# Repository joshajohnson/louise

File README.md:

# Louise

A project between Josh and RiotPunch to build a 75% alice keyboard with a southpaw numpad.

All the PCB files, case dxfs, and QMK firmware required to build your own are located in this repo.

Thanks to [Warmthoughts](https://www.twitch.tv/warmthoughts) for the photo.

## BOM

| Type     | Spec         | Quantity | Notes                                            |
|----------|--------------|----------|--------------------------------------------------|
| Standoff | M2 x 5mm     | 2        | Wrist Wrest                                      |
| Standoff | M2 x 8mm     | 5        | Foot                                             |
| Standoff | M2 x 10mm    | 3        | Wrist Wrest                                      |
| Standoff | M2 x 12mm    | 12       | Case                                             |
| Screw    | M2 x 5mm     | 4        | Wrist Wrest                                      |
| Screw    | M2 x 6mm     | 40       | Everywhere                                       |
| Encoder  | EC11, 15mm   | 1        | PEC11R-4215F-S0024                               |
| Knob     | Max Dia 18mm | 1        | https://www.aliexpress.com/item/33000897896.html |

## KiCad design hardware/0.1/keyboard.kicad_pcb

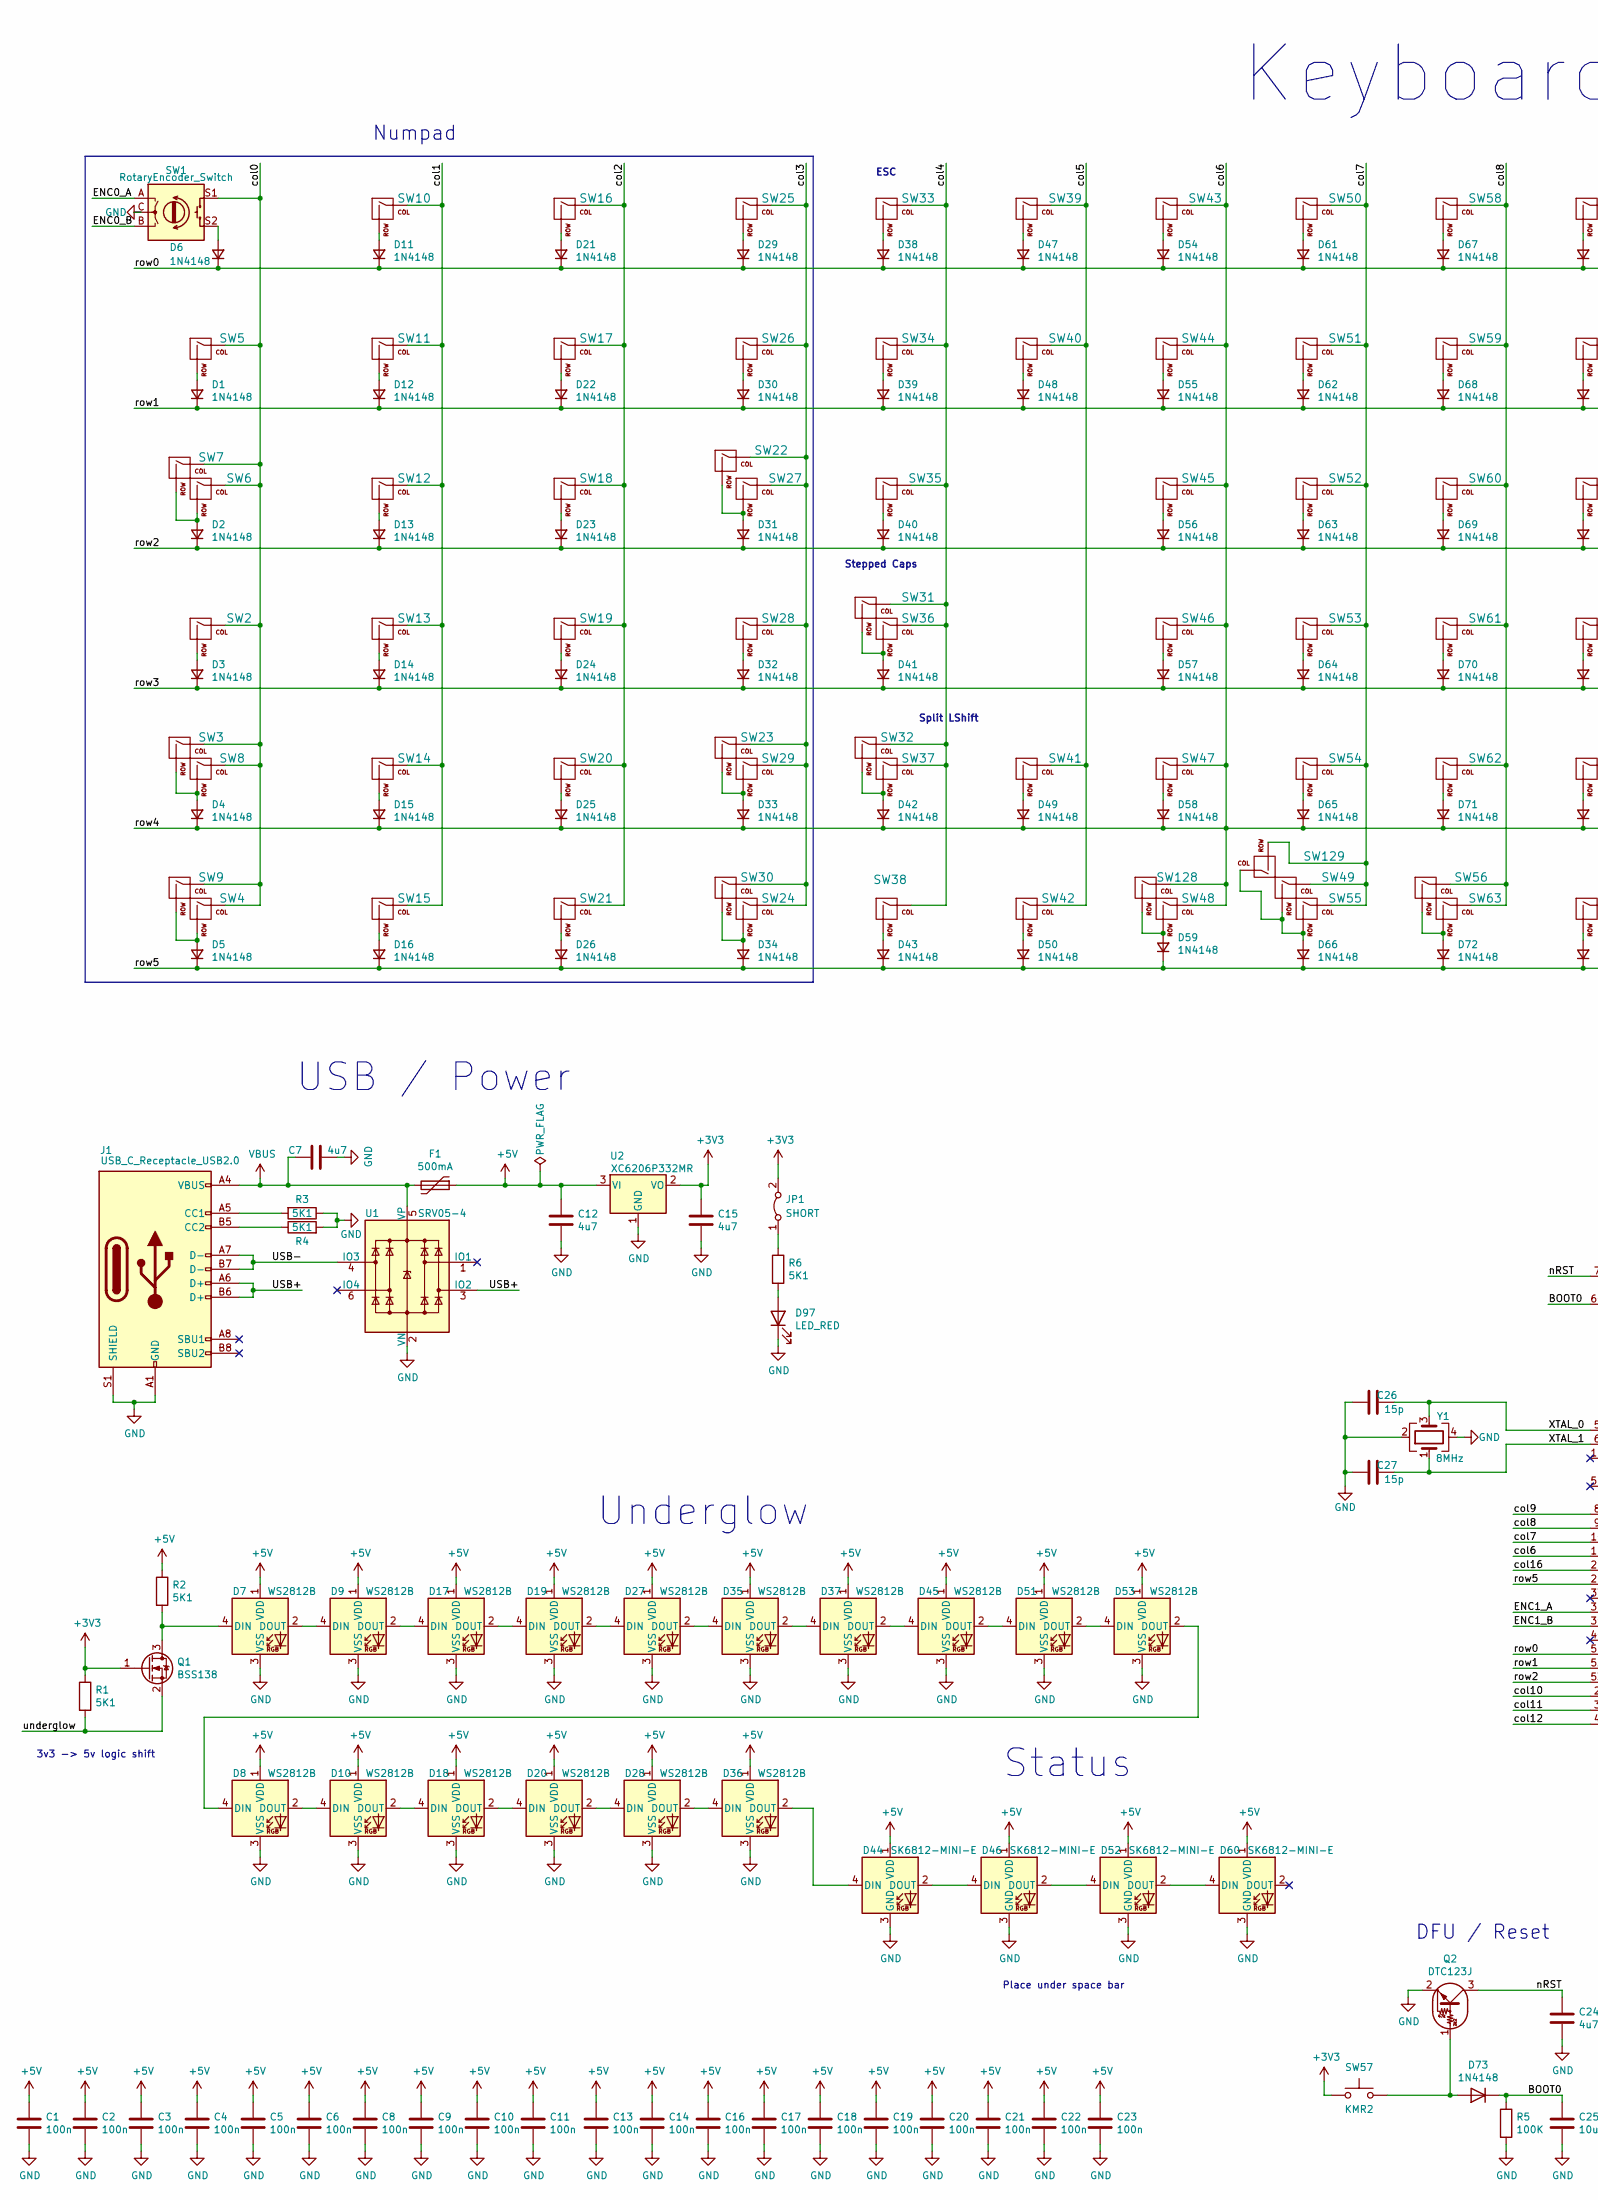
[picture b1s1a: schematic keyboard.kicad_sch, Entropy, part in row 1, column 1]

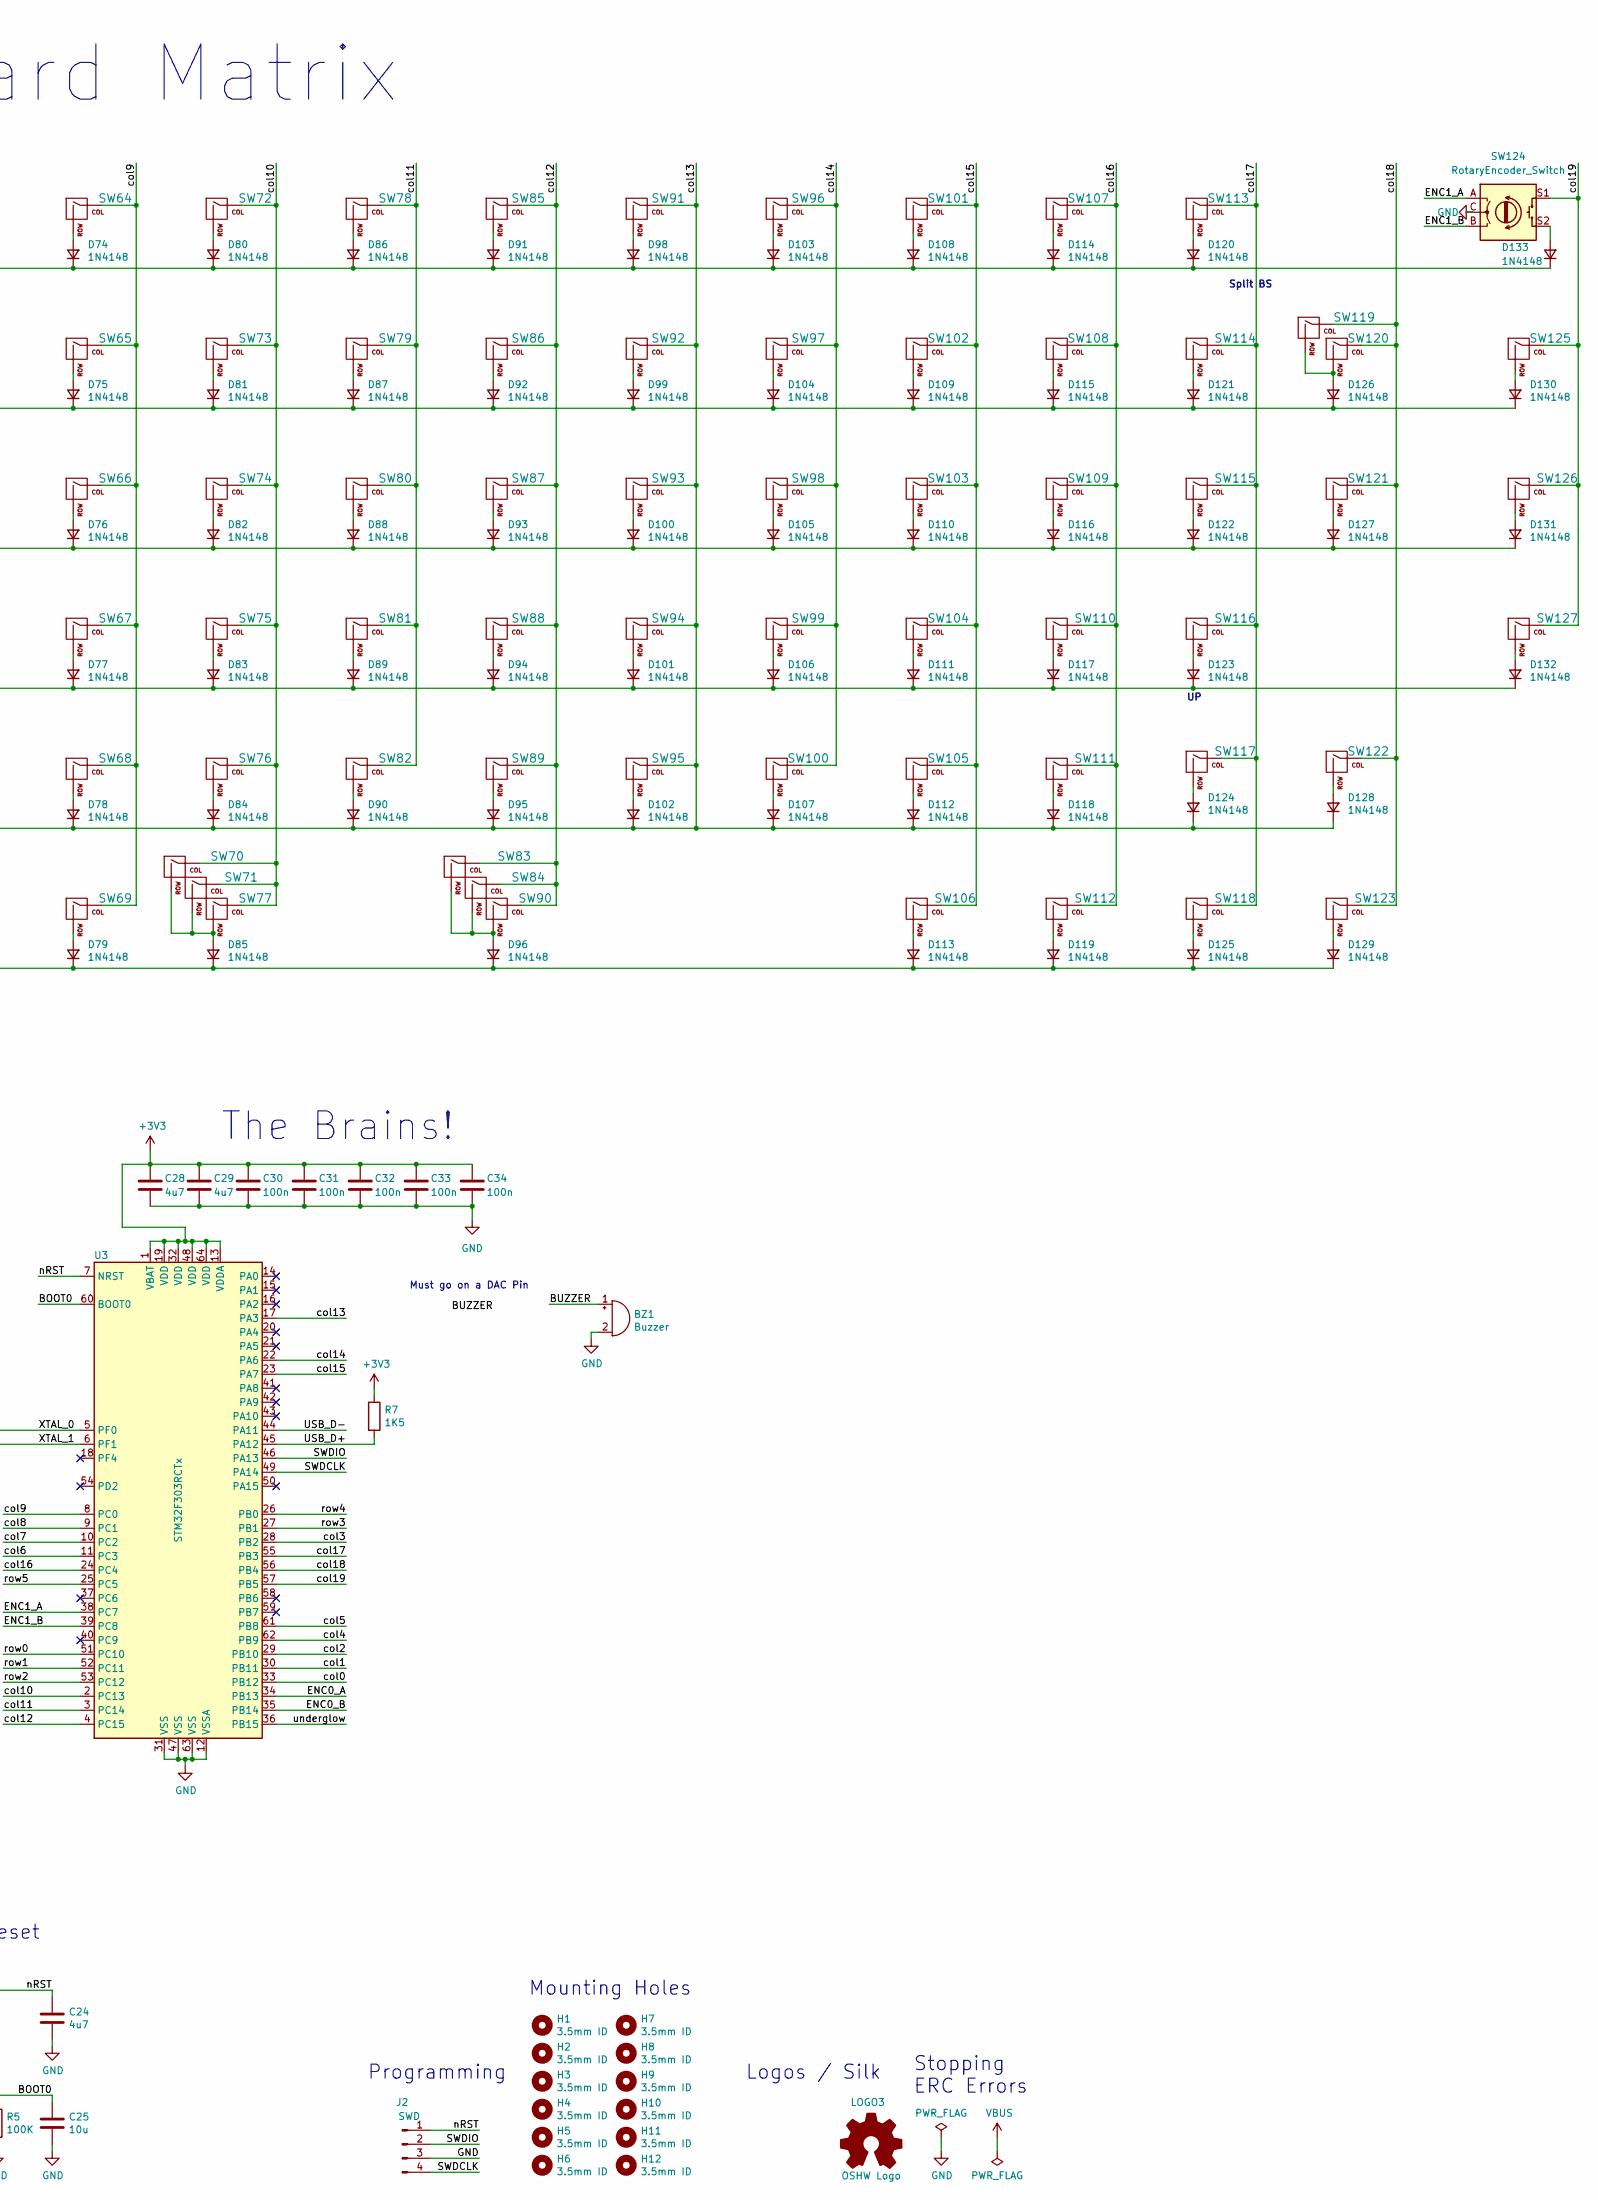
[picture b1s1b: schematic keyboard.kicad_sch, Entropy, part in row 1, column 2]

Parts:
BZ1: Buzzer; Buzzer_Murata_PKMCS0909E
C1, C2, C3, C4, C5, C6, C8, C9, C10, C11, C13, C14, C16, C17, C18, C19, C20, C21, C22, C23, C30, C31, C32, C33, C34: 100n; C_0603_1608Metric
C7, C12, C15, C24, C28, C29: 4u7; C_0603_1608Metric
C25: 10u; C_0603_1608Metric
C26, C27: 15p; C_0603_1608Metric
D1, D2, D3, D4, D5, D6, D11, D12, D13, D14, D15, D16, D21, D22, D23, D24, D25, D26, D29, D30, D31, D32, D33, D34, D38, D39, D40, D41, D42, D43, D47, D48, D49, D50, D54, D55, D56, D57, D58, D59, D61, D62, D63, D64, D65, D66, D67, D68, D69, D70, D71, D72, D73, D74, D75, D76, D77, D78, D79, D80, D81, D82, D83, D84, D85, D86, D87, D88, D89, D90, D91, D92, D93, D94, D95, D96, D98, D99, D100, D101, D102, D103, D104, D105, D106, D107, D108, D109, D110, D111, D112, D113, D114, D115, D116, D117, D118, D119, D120, D121, D122, D123, D124, D125, D126, D127, D128, D129, D130, D131, D132, D133: 1N4148; D_SOD-123
D7, D8, D9, D10, D17, D18, D19, D20, D27, D28, D35, D36, D37, D45, D51, D53: WS2812B; LED_WS2812B_PLCC4_5.0x5.0mm_P3.2mm
D44, D46, D52, D60: SK6812-MINI-E; SK8612-MINI-E
D97: LED_RED; LED_0603_1608Metric
F1: 500mA; Fuse_0805_2012Metric
H1, H2, H3, H4, H5, H6, H7, H8, H9, H10, H11, H12: 3.5mm ID; MountingHole_3.5mm
J1: USB_C_Receptacle_USB2.0; USB_C_Receptacle_HRO_TYPE-C-31-M-12
J2: SWD; 4_PIN_THT_Staggered
JP1: SHORT; SolderJumper-2_P1.3mm_Bridged_RoundedPad1.0x1.5mm
LOGO3: OSHW Logo; OSHW_Logo_3.6x3.6_F.Mask
Q1: BSS138; SOT-23
Q2: DTC123J; SOT-23
R1, R2, R3, R4, R6: 5K1; R_0603_1608Metric
R5: 100K; R_0603_1608Metric
R7: 1K5; R_0603_1608Metric
SW1, SW124: RotaryEncoder_Switch; MX_KEYSWITCH_ENCODER
SW2, SW4, SW5, SW6, SW8, SW10, SW11, SW12, SW13, SW14, SW15, SW16, SW17, SW18, SW19, SW20, SW21, SW24, SW25, SW26, SW27, SW28, SW29, SW33, SW34, SW39, SW40, SW41, SW43, SW44, SW45, SW46, SW47, SW50, SW51, SW52, SW53, SW54, SW56, SW58, SW59, SW60, SW61, SW62, SW64, SW65, SW66, SW67, SW68, SW69, SW72, SW73, SW74, SW75, SW76, SW78, SW79, SW80, SW81, SW82, SW83, SW85, SW86, SW87, SW88, SW89, SW91, SW92, SW93, SW94, SW95, SW96, SW97, SW98, SW99, SW100, SW101, SW102, SW103, SW104, SW105, SW107, SW108, SW109, SW110, SW112, SW113, SW114, SW115, SW118, SW119, SW122, SW123, SW125, SW126, SW127: KEYSW; MXOnly-1U-NoLED
SW3, SW7, SW120: KEYSW; MXOnly-2U-NoLED
SW9, SW22, SW23, SW30, SW55: KEYSW; MXOnly-2U-ReversedStabilizers-NoLED
SW31, SW37, SW42, SW63, SW84, SW128: KEYSW; MXOnly-1.25U-NoLED
SW32, SW49, SW71, SW116, SW129: KEYSW; MXOnly-2.25U-ReversedStabilizers-NoLED
SW35, SW38, SW48, SW90, SW106, SW121: KEYSW; MXOnly-1.5U-NoLED
SW36, SW111, SW117: KEYSW; MXOnly-1.75U-NoLED
SW57: KMR2; SW_Push_KMR2
SW70: KEYSW; MXOnly-3U-ReversedStabilizers-NoLED
SW77: KEYSW; MXOnly-2.75U-ReversedStabilizers-NoLED
U1: SRV05-4; SOT-23-6
U2: XC6206P332MR; SOT-23
U3: STM32F303RCTx; LQFP-64_10x10mm_P0.5mm
Y1: 8MHz; Crystal_SMD_3225-4Pin_3.2x2.5mm

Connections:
+3V3: C15.2, C28.1, C29.1, C30.1, C31.1, C32.1, C33.1, C34.1, JP1.2 (B), Q1.1 (G), R1.1, R7.1, SW57.1, U2.2 (VO), U3.1 (VBAT), U3.13 (VDDA), U3.19 (VDD), U3.32 (VDD), U3.48 (VDD), U3.64 (VDD)
+5V: C1.2, C2.2, C3.2, C4.2, C5.2, C6.2, C8.2, C9.2, C10.2, C11.2, C12.2, C13.2, C14.2, C16.2, C17.2, C18.2, C19.2, C20.2, C21.2, C22.2, C23.2, D7.1 (VDD), D8.1 (VDD), D9.1 (VDD), D10.1 (VDD), D17.1 (VDD), D18.1 (VDD), D19.1 (VDD), D20.1 (VDD), D27.1 (VDD), D28.1 (VDD), D35.1 (VDD), D36.1 (VDD), D37.1 (VDD), D44.1 (VDD), D45.1 (VDD), D46.1 (VDD), D51.1 (VDD), D52.1 (VDD), D53.1 (VDD), D60.1 (VDD), F1.1, R2.1, U2.3 (VI)
/BOOT0: C25.1, D73.1 (K), R5.1, U3.60 (BOOT0)
/BUZZER: BZ1.1 (-)
/ENC0_A: SW1.A, U3.34 (PB13)
/ENC0_B: SW1.B, U3.35 (PB14)
/ENC1_A: SW124.A, U3.38 (PC7)
/ENC1_B: SW124.B, U3.39 (PC8)
/SWDCLK: J2.4, U3.49 (PA14)
/SWDIO: J2.2, U3.46 (PA13)
/USB+: J1.A6 (D+), J1.B6 (D+), U1.3 (IO2)
/USB-: J1.A7 (D-), J1.B7 (D-), U1.4 (IO3)
/USB_D+: R7.2, U3.45 (PA12)
/USB_D-: U3.44 (PA11)
/XTAL_0: C26.1, U3.5 (PF0), Y1.3
/XTAL_1: C27.1, U3.6 (PF1), Y1.1
/col0: SW1.S1, SW2.1 (COL), SW3.1 (COL), SW4.1 (COL), SW5.1 (COL), SW6.1 (COL), SW7.1 (COL), SW8.1 (COL), SW9.1 (COL), U3.33 (PB12)
/col1: SW10.1 (COL), SW11.1 (COL), SW12.1 (COL), SW13.1 (COL), SW14.1 (COL), SW15.1 (COL), U3.30 (PB11)
/col2: SW16.1 (COL), SW17.1 (COL), SW18.1 (COL), SW19.1 (COL), SW20.1 (COL), SW21.1 (COL), U3.29 (PB10)
/col3: SW22.1 (COL), SW23.1 (COL), SW24.1 (COL), SW25.1 (COL), SW26.1 (COL), SW27.1 (COL), SW28.1 (COL), SW29.1 (COL), SW30.1 (COL), U3.28 (PB2)
/col4: SW31.1 (COL), SW32.1 (COL), SW33.1 (COL), SW34.1 (COL), SW35.1 (COL), SW36.1 (COL), SW37.1 (COL), SW38.1 (COL), U3.62 (PB9)
/col5: SW39.1 (COL), SW40.1 (COL), SW41.1 (COL), SW42.1 (COL), U3.61 (PB8)
/col7: SW49.1 (COL), SW50.1 (COL), SW51.1 (COL), SW52.1 (COL), SW53.1 (COL), SW54.1 (COL), SW55.1 (COL), SW129.2 (ROW), U3.10 (PC2)
/col8: SW56.1 (COL), SW58.1 (COL), SW59.1 (COL), SW60.1 (COL), SW61.1 (COL), SW62.1 (COL), SW63.1 (COL), U3.9 (PC1)
/col9: SW64.1 (COL), SW65.1 (COL), SW66.1 (COL), SW67.1 (COL), SW68.1 (COL), SW69.1 (COL), U3.8 (PC0)
/col10: SW70.1 (COL), SW71.1 (COL), SW72.1 (COL), SW73.1 (COL), SW74.1 (COL), SW75.1 (COL), SW76.1 (COL), SW77.1 (COL), U3.2 (PC13)
/col11: SW78.1 (COL), SW79.1 (COL), SW80.1 (COL), SW81.1 (COL), SW82.1 (COL), U3.3 (PC14)
/col12: SW83.1 (COL), SW84.1 (COL), SW85.1 (COL), SW86.1 (COL), SW87.1 (COL), SW88.1 (COL), SW89.1 (COL), SW90.1 (COL), U3.4 (PC15)
/col13: D4.1 (K), D15.1 (K), D25.1 (K), D33.1 (K), D42.1 (K), D49.1 (K), D58.1 (K), D65.1 (K), D71.1 (K), D78.1 (K), D84.1 (K), D90.1 (K), D95.1 (K), D102.1 (K), D107.1 (K), D112.1 (K), D118.1 (K), D124.1 (K), D128.1 (K), SW43.1 (COL), SW44.1 (COL), SW45.1 (COL), SW46.1 (COL), SW47.1 (COL), SW48.1 (COL), SW91.1 (COL), SW92.1 (COL), SW93.1 (COL), SW94.1 (COL), SW95.1 (COL), SW128.1 (COL), U3.11 (PC3), U3.17 (PA3), U3.26 (PB0)
/col14: SW96.1 (COL), SW97.1 (COL), SW98.1 (COL), SW99.1 (COL), SW100.1 (COL), U3.22 (PA6)
/col15: SW101.1 (COL), SW102.1 (COL), SW103.1 (COL), SW104.1 (COL), SW105.1 (COL), SW106.1 (COL), U3.23 (PA7)
/col16: SW107.1 (COL), SW108.1 (COL), SW109.1 (COL), SW110.1 (COL), SW111.1 (COL), SW112.1 (COL), U3.24 (PC4)
/col17: SW113.1 (COL), SW114.1 (COL), SW115.1 (COL), SW116.1 (COL), SW117.1 (COL), SW118.1 (COL), U3.55 (PB3)
/col18: SW119.1 (COL), SW120.1 (COL), SW121.1 (COL), SW122.1 (COL), SW123.1 (COL), U3.56 (PB4)
/col19: SW124.S1, SW125.1 (COL), SW126.1 (COL), SW127.1 (COL), U3.57 (PB5)
/nRST: C24.1, J2.1, Q2.3 (C), U3.7 (NRST)
/row0: D6.1 (K), D11.1 (K), D21.1 (K), D29.1 (K), D38.1 (K), D47.1 (K), D54.1 (K), D61.1 (K), D67.1 (K), D74.1 (K), D80.1 (K), D86.1 (K), D91.1 (K), D98.1 (K), D103.1 (K), D108.1 (K), D114.1 (K), D120.1 (K), D133.1 (K), U3.51 (PC10)
/row1: D1.1 (K), D12.1 (K), D22.1 (K), D30.1 (K), D39.1 (K), D48.1 (K), D55.1 (K), D62.1 (K), D68.1 (K), D75.1 (K), D81.1 (K), D87.1 (K), D92.1 (K), D99.1 (K), D104.1 (K), D109.1 (K), D115.1 (K), D121.1 (K), D126.1 (K), D130.1 (K), U3.52 (PC11)
/row2: D2.1 (K), D13.1 (K), D23.1 (K), D31.1 (K), D40.1 (K), D56.1 (K), D63.1 (K), D69.1 (K), D76.1 (K), D82.1 (K), D88.1 (K), D93.1 (K), D100.1 (K), D105.1 (K), D110.1 (K), D116.1 (K), D122.1 (K), D127.1 (K), D131.1 (K), U3.53 (PC12)
/row3: D3.1 (K), D14.1 (K), D24.1 (K), D32.1 (K), D41.1 (K), D57.1 (K), D64.1 (K), D70.1 (K), D77.1 (K), D83.1 (K), D89.1 (K), D94.1 (K), D101.1 (K), D106.1 (K), D111.1 (K), D117.1 (K), D123.1 (K), D132.1 (K), U3.27 (PB1)
/row5: D5.1 (K), D16.1 (K), D26.1 (K), D34.1 (K), D43.1 (K), D50.1 (K), D59.1 (K), D66.1 (K), D72.1 (K), D79.1 (K), D85.1 (K), D96.1 (K), D113.1 (K), D119.1 (K), D125.1 (K), D129.1 (K), U3.25 (PC5)
/underglow: Q1.2 (S), R1.2, U3.36 (PB15)
GND: BZ1.2 (+), C1.1, C2.1, C3.1, C4.1, C5.1, C6.1, C7.1, C8.1, C9.1, C10.1, C11.1, C12.1, C13.1, C14.1, C15.1, C16.1, C17.1, C18.1, C19.1, C20.1, C21.1, C22.1, C23.1, C24.2, C25.2, C26.2, C27.2, C28.2, C29.2, C30.2, C31.2, C32.2, C33.2, C34.2, D7.3 (VSS), D8.3 (VSS), D9.3 (VSS), D10.3 (VSS), D17.3 (VSS), D18.3 (VSS), D19.3 (VSS), D20.3 (VSS), D27.3 (VSS), D28.3 (VSS), D35.3 (VSS), D36.3 (VSS), D37.3 (VSS), D44.3 (GND), D45.3 (VSS), D46.3 (GND), D51.3 (VSS), D52.3 (GND), D53.3 (VSS), D60.3 (GND), D97.1 (K), J1.A1 (GND), J1.A12 (GND), J1.B1 (GND), J1.B12 (GND), J1.S1 (SHIELD), J2.3, Q2.2 (E), R3.1, R4.2, R5.2, SW1.C, SW124.C, U1.2 (VN), U2.1 (GND), U3.12 (VSSA), U3.31 (VSS), U3.47 (VSS), U3.63 (VSS), Y1.2, Y1.4
unnamed: D1.2 (A), SW5.2 (ROW)
unnamed: D2.2 (A), SW6.2 (ROW), SW7.2 (ROW)
unnamed: D3.2 (A), SW2.2 (ROW)
unnamed: D4.2 (A), SW3.2 (ROW), SW8.2 (ROW)
unnamed: D5.2 (A), SW4.2 (ROW), SW9.2 (ROW)
unnamed: D6.2 (A), SW1.S2
unnamed: D7.2 (DOUT), D9.4 (DIN)
unnamed: D7.4 (DIN), Q1.3 (D), R2.2
unnamed: D10.2 (DOUT), D18.4 (DIN)
unnamed: D8.2 (DOUT), D10.4 (DIN)
unnamed: D11.2 (A), SW10.2 (ROW)
unnamed: D12.2 (A), SW11.2 (ROW)
unnamed: D13.2 (A), SW12.2 (ROW)
unnamed: D14.2 (A), SW13.2 (ROW)
unnamed: D15.2 (A), SW14.2 (ROW)
unnamed: D16.2 (A), SW15.2 (ROW)
unnamed: D17.2 (DOUT), D19.4 (DIN)
unnamed: D9.2 (DOUT), D17.4 (DIN)
unnamed: D18.2 (DOUT), D20.4 (DIN)
unnamed: D19.2 (DOUT), D27.4 (DIN)
unnamed: D20.2 (DOUT), D28.4 (DIN)
unnamed: D21.2 (A), SW16.2 (ROW)
unnamed: D22.2 (A), SW17.2 (ROW)
unnamed: D23.2 (A), SW18.2 (ROW)
unnamed: D24.2 (A), SW19.2 (ROW)
unnamed: D25.2 (A), SW20.2 (ROW)
unnamed: D26.2 (A), SW21.2 (ROW)
unnamed: D27.2 (DOUT), D35.4 (DIN)
unnamed: D28.2 (DOUT), D36.4 (DIN)
unnamed: D29.2 (A), SW25.2 (ROW)
unnamed: D30.2 (A), SW26.2 (ROW)
unnamed: D31.2 (A), SW22.2 (ROW), SW27.2 (ROW)
unnamed: D32.2 (A), SW28.2 (ROW)
unnamed: D33.2 (A), SW23.2 (ROW), SW29.2 (ROW)
unnamed: D34.2 (A), SW24.2 (ROW), SW30.2 (ROW)
unnamed: D35.2 (DOUT), D37.4 (DIN)
unnamed: D36.2 (DOUT), D44.4 (DIN)
unnamed: D37.2 (DOUT), D45.4 (DIN)
unnamed: D38.2 (A), SW33.2 (ROW)
unnamed: D39.2 (A), SW34.2 (ROW)
unnamed: D40.2 (A), SW35.2 (ROW)
unnamed: D41.2 (A), SW31.2 (ROW), SW36.2 (ROW)
unnamed: D42.2 (A), SW32.2 (ROW), SW37.2 (ROW)
unnamed: D43.2 (A), SW38.2 (ROW)
unnamed: D44.2 (DOUT), D46.4 (DIN)
unnamed: D45.2 (DOUT), D51.4 (DIN)
unnamed: D46.2 (DOUT), D52.4 (DIN)
unnamed: D47.2 (A), SW39.2 (ROW)
unnamed: D48.2 (A), SW40.2 (ROW)
unnamed: D49.2 (A), SW41.2 (ROW)
unnamed: D50.2 (A), SW42.2 (ROW)
unnamed: D51.2 (DOUT), D53.4 (DIN)
unnamed: D52.2 (DOUT), D60.4 (DIN)
unnamed: D8.4 (DIN), D53.2 (DOUT)
unnamed: D54.2 (A), SW43.2 (ROW)
unnamed: D55.2 (A), SW44.2 (ROW)
unnamed: D56.2 (A), SW45.2 (ROW)
unnamed: D57.2 (A), SW46.2 (ROW)
unnamed: D58.2 (A), SW47.2 (ROW)
unnamed: D59.2 (A), SW48.2 (ROW), SW128.2 (ROW)
unnamed: D61.2 (A), SW50.2 (ROW)
unnamed: D62.2 (A), SW51.2 (ROW)
unnamed: D63.2 (A), SW52.2 (ROW)
unnamed: D64.2 (A), SW53.2 (ROW)
unnamed: D65.2 (A), SW54.2 (ROW)
unnamed: D66.2 (A), SW49.2 (ROW), SW55.2 (ROW), SW129.1 (COL)
unnamed: D67.2 (A), SW58.2 (ROW)
unnamed: D68.2 (A), SW59.2 (ROW)
unnamed: D69.2 (A), SW60.2 (ROW)
unnamed: D70.2 (A), SW61.2 (ROW)
unnamed: D71.2 (A), SW62.2 (ROW)
unnamed: D72.2 (A), SW56.2 (ROW), SW63.2 (ROW)
unnamed: D73.2 (A), Q2.1 (B), SW57.2
unnamed: D74.2 (A), SW64.2 (ROW)
unnamed: D75.2 (A), SW65.2 (ROW)
unnamed: D76.2 (A), SW66.2 (ROW)
unnamed: D77.2 (A), SW67.2 (ROW)
unnamed: D78.2 (A), SW68.2 (ROW)
unnamed: D79.2 (A), SW69.2 (ROW)
unnamed: D80.2 (A), SW72.2 (ROW)
unnamed: D81.2 (A), SW73.2 (ROW)
unnamed: D82.2 (A), SW74.2 (ROW)
unnamed: D83.2 (A), SW75.2 (ROW)
unnamed: D84.2 (A), SW76.2 (ROW)
unnamed: D85.2 (A), SW70.2 (ROW), SW71.2 (ROW), SW77.2 (ROW)
unnamed: D86.2 (A), SW78.2 (ROW)
unnamed: D87.2 (A), SW79.2 (ROW)
unnamed: D88.2 (A), SW80.2 (ROW)
unnamed: D89.2 (A), SW81.2 (ROW)
unnamed: D90.2 (A), SW82.2 (ROW)
unnamed: D91.2 (A), SW85.2 (ROW)
unnamed: D92.2 (A), SW86.2 (ROW)
unnamed: D93.2 (A), SW87.2 (ROW)
unnamed: D94.2 (A), SW88.2 (ROW)
unnamed: D95.2 (A), SW89.2 (ROW)
unnamed: D96.2 (A), SW83.2 (ROW), SW84.2 (ROW), SW90.2 (ROW)
unnamed: D97.2 (A), R6.2
unnamed: D98.2 (A), SW91.2 (ROW)
unnamed: D99.2 (A), SW92.2 (ROW)
unnamed: D100.2 (A), SW93.2 (ROW)
unnamed: D101.2 (A), SW94.2 (ROW)
unnamed: D102.2 (A), SW95.2 (ROW)
unnamed: D103.2 (A), SW96.2 (ROW)
unnamed: D104.2 (A), SW97.2 (ROW)
unnamed: D105.2 (A), SW98.2 (ROW)
unnamed: D106.2 (A), SW99.2 (ROW)
unnamed: D107.2 (A), SW100.2 (ROW)
unnamed: D108.2 (A), SW101.2 (ROW)
unnamed: D109.2 (A), SW102.2 (ROW)
unnamed: D110.2 (A), SW103.2 (ROW)
unnamed: D111.2 (A), SW104.2 (ROW)
unnamed: D112.2 (A), SW105.2 (ROW)
unnamed: D113.2 (A), SW106.2 (ROW)
unnamed: D114.2 (A), SW107.2 (ROW)
unnamed: D115.2 (A), SW108.2 (ROW)
unnamed: D116.2 (A), SW109.2 (ROW)
unnamed: D117.2 (A), SW110.2 (ROW)
unnamed: D118.2 (A), SW111.2 (ROW)
unnamed: D119.2 (A), SW112.2 (ROW)
unnamed: D120.2 (A), SW113.2 (ROW)
unnamed: D121.2 (A), SW114.2 (ROW)
unnamed: D122.2 (A), SW115.2 (ROW)
unnamed: D123.2 (A), SW116.2 (ROW)
unnamed: D124.2 (A), SW117.2 (ROW)
unnamed: D125.2 (A), SW118.2 (ROW)
unnamed: D126.2 (A), SW119.2 (ROW), SW120.2 (ROW)
unnamed: D127.2 (A), SW121.2 (ROW)
unnamed: D128.2 (A), SW122.2 (ROW)
unnamed: D129.2 (A), SW123.2 (ROW)
unnamed: D130.2 (A), SW125.2 (ROW)
unnamed: D131.2 (A), SW126.2 (ROW)
unnamed: D132.2 (A), SW127.2 (ROW)
unnamed: D133.2 (A), SW124.S2
unnamed: J1.A5 (CC1), R3.2
unnamed: J1.B5 (CC2), R4.1
unnamed: JP1.1 (A), R6.1
VBUS: C7.2, F1.2, J1.A4 (VBUS), J1.A9 (VBUS), J1.B4 (VBUS), J1.B9 (VBUS), U1.5 (VP)

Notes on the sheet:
USB / Power
Keyboard Matrix
3v3 -> 5v logic shift
Place under space bar
Stepped Caps
DFU / Reset
Programming
Numpad
Stopping ERC Errors
Split BS
Must go on a DAC Pin
Split LShift
Logos / Silk
ESC
The Brains!
Underglow
Status
Mounting Holes

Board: 2 copper layers, 327 parts (1 on the bottom side), 178 nets, no tracks yet.

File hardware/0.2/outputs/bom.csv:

Item,Qty,Reference(s),Value,LibPart,Footprint,LCSC,MPN,Manufacturer
1,1,BZ1,Buzzer,Device:Buzzer,josh-mechanical:Buzzer_Murata_PKMCS0909E,,PKMCS0909E,Murata Electronics
2,27,"C1, C2, C3, C4, C5, C6, C8, C9, C10, C11, C13, C14, C16, C17, C18, C19, C20, C21, C22, C23, C30, C31, C32, C33, C34, C35, C36",100n,Device:C,Capacitor_SMD:C_0603_1608Metric,C14663,CC0603KRX7R9BB104,YAGEO
3,6,"C7, C12, C15, C24, C28, C29",4u7,Device:C,Capacitor_SMD:C_0603_1608Metric,C19666,CL10A475KO8NNNC,Samsung Electro-Mechanics
4,1,C25,10u,Device:C,Capacitor_SMD:C_0603_1608Metric,C96446,CL10A106MA8NRNC,Samsung Electro-Mechanics
5,2,"C26, C27",15p,Device:C,Capacitor_SMD:C_0603_1608Metric,C1644,CL10C150JB8NNNC,Samsung Electro-Mechanics
6,111,"D1, D2, D3, D4, D5, D6, D11, D12, D13, D14, D15, D16, D21, D22, D23, D24, D25, D26, D29, D30, D31, D32, D33, D34, D38, D39, D40, D41, D42, D43, D47, D48, D49, D50, D54, D55, D56, D57, D58, D59, D61, D62, D63, D64, D65, D66, D67, D68, D69, D70, D71, D72, D74, D75, D76, D77, D78, D79, D80, D81, D82, D83, D84, D85, D86, D87, D88, D89, D90, D91, D92, D93, D94, D95, D96, D98, D99, D100, D101, D102, D103, D104, D105, D106, D107, D108, D109, D110, D111, D112, D113, D114, D115, D116, D117, D118, D119, D120, D121, D122, D123, D124, D125, D126, D127, D128, D129, D130, D131, D132, D133",1N4148,Device:D_Small,Diode_SMD:D_SOD-123,C81598,1N4148W,Semtech
7,18,"D7, D8, D9, D10, D17, D18, D19, D20, D27, D28, D35, D36, D37, D45, D51, D53, D134, D135",WS2812B,LED:WS2812B,LED_SMD:LED_WS2812B_PLCC4_5.0x5.0mm_P3.2mm,C2761795,WS2812B-B/W,Worldsemi
8,4,"D44, D46, D52, D60",SK6812-MINI-E,josh-led:SK6812-MINI-E,josh-led:SK8612-MINI-E,,SK6812-MINI-E,Shenzhen LED Color
9,1,D73,1N4148,Device:D,Diode_SMD:D_SOD-123,C81598,1N4148W,Semtech
10,1,D97,BLUE,Device:LED,LED_SMD:LED_0603_1608Metric,C72041,19-217/BHC-ZL1M2RY/3T ,Everlight Elec
11,1,F1,500mA,Device:Polyfuse,josh-passives-smt:Fuse_0805_2012Metric,C66452,SMD0805-050,TECHFUSE
12,1,J1,USB_C_Receptacle_USB2.0,Connector:USB_C_Receptacle_USB2.0,josh-connectors:USB_C_Receptacle_HRO_TYPE-C-31-M-12,C165948,TYPE-C-31-M-12,Korean Hroparts Elec
14,1,Q1,2N7002,Transistor_FET:BSS138,Package_TO_SOT_SMD:SOT-23,C8545,2N7002,Changjiang Electronics Tech (CJ)
15,1,Q2,DTC123J,Transistor_BJT:DTC123J,Package_TO_SOT_SMD:SOT-23,C145108,DDTC123JCA-7-F,Diodes Incorporated
16,5,"R1, R2, R3, R4, R6",5K1,Device:R,Resistor_SMD:R_0603_1608Metric,C23186,0603WAF5101T5E,UNI-ROYAL(Uniroyal Elec)
17,1,R5,100K,Device:R,Resistor_SMD:R_0603_1608Metric,C25803,0603WAF1003T5E,UNI-ROYAL(Uniroyal Elec)
18,1,R7,1K5,Device:R,Resistor_SMD:R_0603_1608Metric,C22843,0603WAF1501T5E,UNI-ROYAL(Uniroyal Elec)
19,1,R8,22R,Device:R,Resistor_SMD:R_0603_1608Metric,C23345,0603WAF220JT5E,UNI-ROYAL(Uniroyal Elec)
29,1,SW57,KMR2,Switch:SW_Push,josh-buttons-switches:SW_Push_KMR2,C99271,KMR231GLFS,C&K
32,1,U1,SRV05-4,Power_Protection:SRV05-4,Package_TO_SOT_SMD:SOT-23-6,C85364,XC6206P332MR,ProTek Devices
33,1,U2,XC6206P332MR,Regulator_Linear:XC6206PxxxMR,Package_TO_SOT_SMD:SOT-23,C5446,XC6206P332MR,Torex Semicon
34,1,U3,STM32F303RBT6,MCU_ST_STM32F3:STM32F303RCTx,Package_QFP:LQFP-64_10x10mm_P0.5mm,C130453,STM32F303RBT6,STMicroelectronics
35,1,Y1,8MHz,Device:Crystal_GND24,josh-oscillators:Crystal_SMD_3225-4Pin_3.2x2.5mm,C403948,TAXM8M4RFDCET2T,TAE(Zhejiang Abel Elec)

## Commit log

2021-12-30 init
2021-12-30 starting afresh
2021-12-31 WIP layout
2021-12-31 schematic had unsaved changes
2022-01-01 first pass layout
2022-01-03 added more LEDs
2022-01-04 clean up traces, silk TODO
2022-01-05 add silk
2022-01-07 0.1 off to fab
2022-02-24 tripup numpad usb
2022-05-11 add laser cutter files
2022-05-11 add fw
2022-05-20 Add QMK firmware source code.
2022-05-21 add laser cutter files and josh keymap
2022-05-21 add readme photo
2022-07-13 bom fix
2022-07-17 move usb connecor location for 0.2
2022-07-29 update top layer dxf and make piezo louder
2022-08-13 update plate and bom
2022-10-06 update bom
2024-07-04 Layer 7 acrylic updated for recessed USB connector
